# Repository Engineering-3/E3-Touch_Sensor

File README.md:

# E3-Touch_Sensor

This is the momentary switch used with the Engineering^3 curriculum and RCM Control Stack. Please see [Engineering3](http://engineering3.org/) for more information on the complete RCM Control Stack project.

Repository Contents
-------------------

* **/E3-Touch_v1_3/** - Eagle schematic/board files, gerbers, and BOM

Version History
---------------
* [E3-Touch_v1_3](https://github.com/Engineering-3/E3-Touch_Sensor/tree/master/E3-Touch_Sensor_v1)- First released version

License Information
-------------------
Hardware is released under [Solderpad Hardware License v0.51](http://solderpad.org/licenses/SHL-0.51/).
Distributed as-is; no warranty is given.

Getting Started Help
--------------------
This is a Plug-n-Play board.

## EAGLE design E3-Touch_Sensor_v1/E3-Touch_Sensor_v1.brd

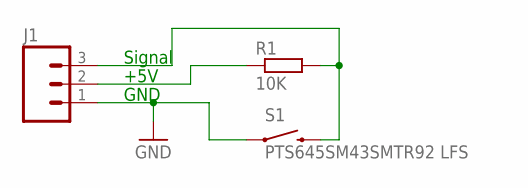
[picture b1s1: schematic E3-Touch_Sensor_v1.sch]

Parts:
J1: M03PTH; 1X03
R1: 10K; R0603
S1: PTS645SM43SMTR92 LFS; TACTILE_SWITCH_TALL

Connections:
GND: J1.1, S1.A2 (1)
unnamed: J1.3, R1.2, S1.B2 (2)
unnamed: J1.2, R1.1

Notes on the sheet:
+5V
Signal
GND

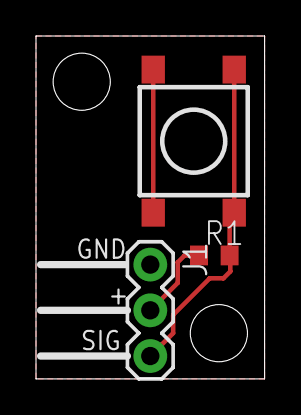
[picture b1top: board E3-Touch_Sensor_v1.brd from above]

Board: 2 copper layers, 12.7 x 19.1 mm, 3 parts (0 on the bottom side), 3 nets.

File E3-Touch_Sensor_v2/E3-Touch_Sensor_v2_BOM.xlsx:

E3-Touch_Sensor_v1 BOM
Item # | Qty | Ref Des | Manufacturer | Mfg Part # | Dist. Part # | Description | Package | Type
1 | 1 | R1 | Yageo | RC0603JR-0710KL | 311-10KGRCT-ND | RES SMD 10K OHM 5% 1/10W 0603 | 603 | SMT
2 | 1 | S1 | C&K | PTS645SM43SMTR92 LFS | CKN9112CT-ND | SWITCH TACTILE SPST-NO 0.05A 12V | 6mm x 6mm | SMT
3 | 1 | J1 | Wurth Electronics Inc. | 61300311021 | 732-5336-ND | CONN HEADER 3 POS RA 2.54 | header | PTH
 |  |  |  |  |  | BOARD SUMMARY FOR QUOTE
 |  |  |  |  |  | Unique Part Count | 32
 |  |  |  |  |  | Total Placements | 266
 |  |  |  |  |  | Thru Hole Placements | 10
 |  |  |  |  |  | Has BGA Placements? | No
 |  |  |  |  |  |  |  | 1140 NW Third Ave.
 |  |  |  |  |  |  |  | Canby, OR 97013

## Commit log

2017-05-28 Adding v1 of Touch Sensor board.
2017-07-14 Touch Sensor v1 and v2, after changes to bottom silk on V2 for being clear about reversal ability.
2017-08-07 Final version sent to fab.
2017-12-04 Added dimensions.
2017-12-04 Added more dimensions.

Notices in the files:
parts and their libraries:
SparkFun-Connectors: Licensing: Creative Commons ShareAlike 4.0 International - https://creativecommons.org/licenses/by-sa/4.0
